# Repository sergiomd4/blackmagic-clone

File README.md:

Black Magic Clone
========================================

Black Magic is an easy-to-use board used for debugging embedded microcontrollers. It supports several targets from manufacturers such as STMicroelectronics, Atmel, Nordic Semiconductor, NXP, Texas Instruments, Freescale, Silicon Labs, Xilinx or Raspberry Pi.

GNU debugger
-------------------
The Black Magic GNU DeBugger (GDB) server features:
* Automatic target detection
* No need for target specific configuration scripts
* Easily scriptable
* Interface to the host computer does not require special drivers
* Full debugging functionality
* Works with Windows, Linux and Mac environments

Repository Contents
-------------------

* **/Production** - Gerber files, drill files, BOM, CPL file
* **/Hardware** - KiCad PCB files, footprints library
* **/Documents** - Schematics pdf

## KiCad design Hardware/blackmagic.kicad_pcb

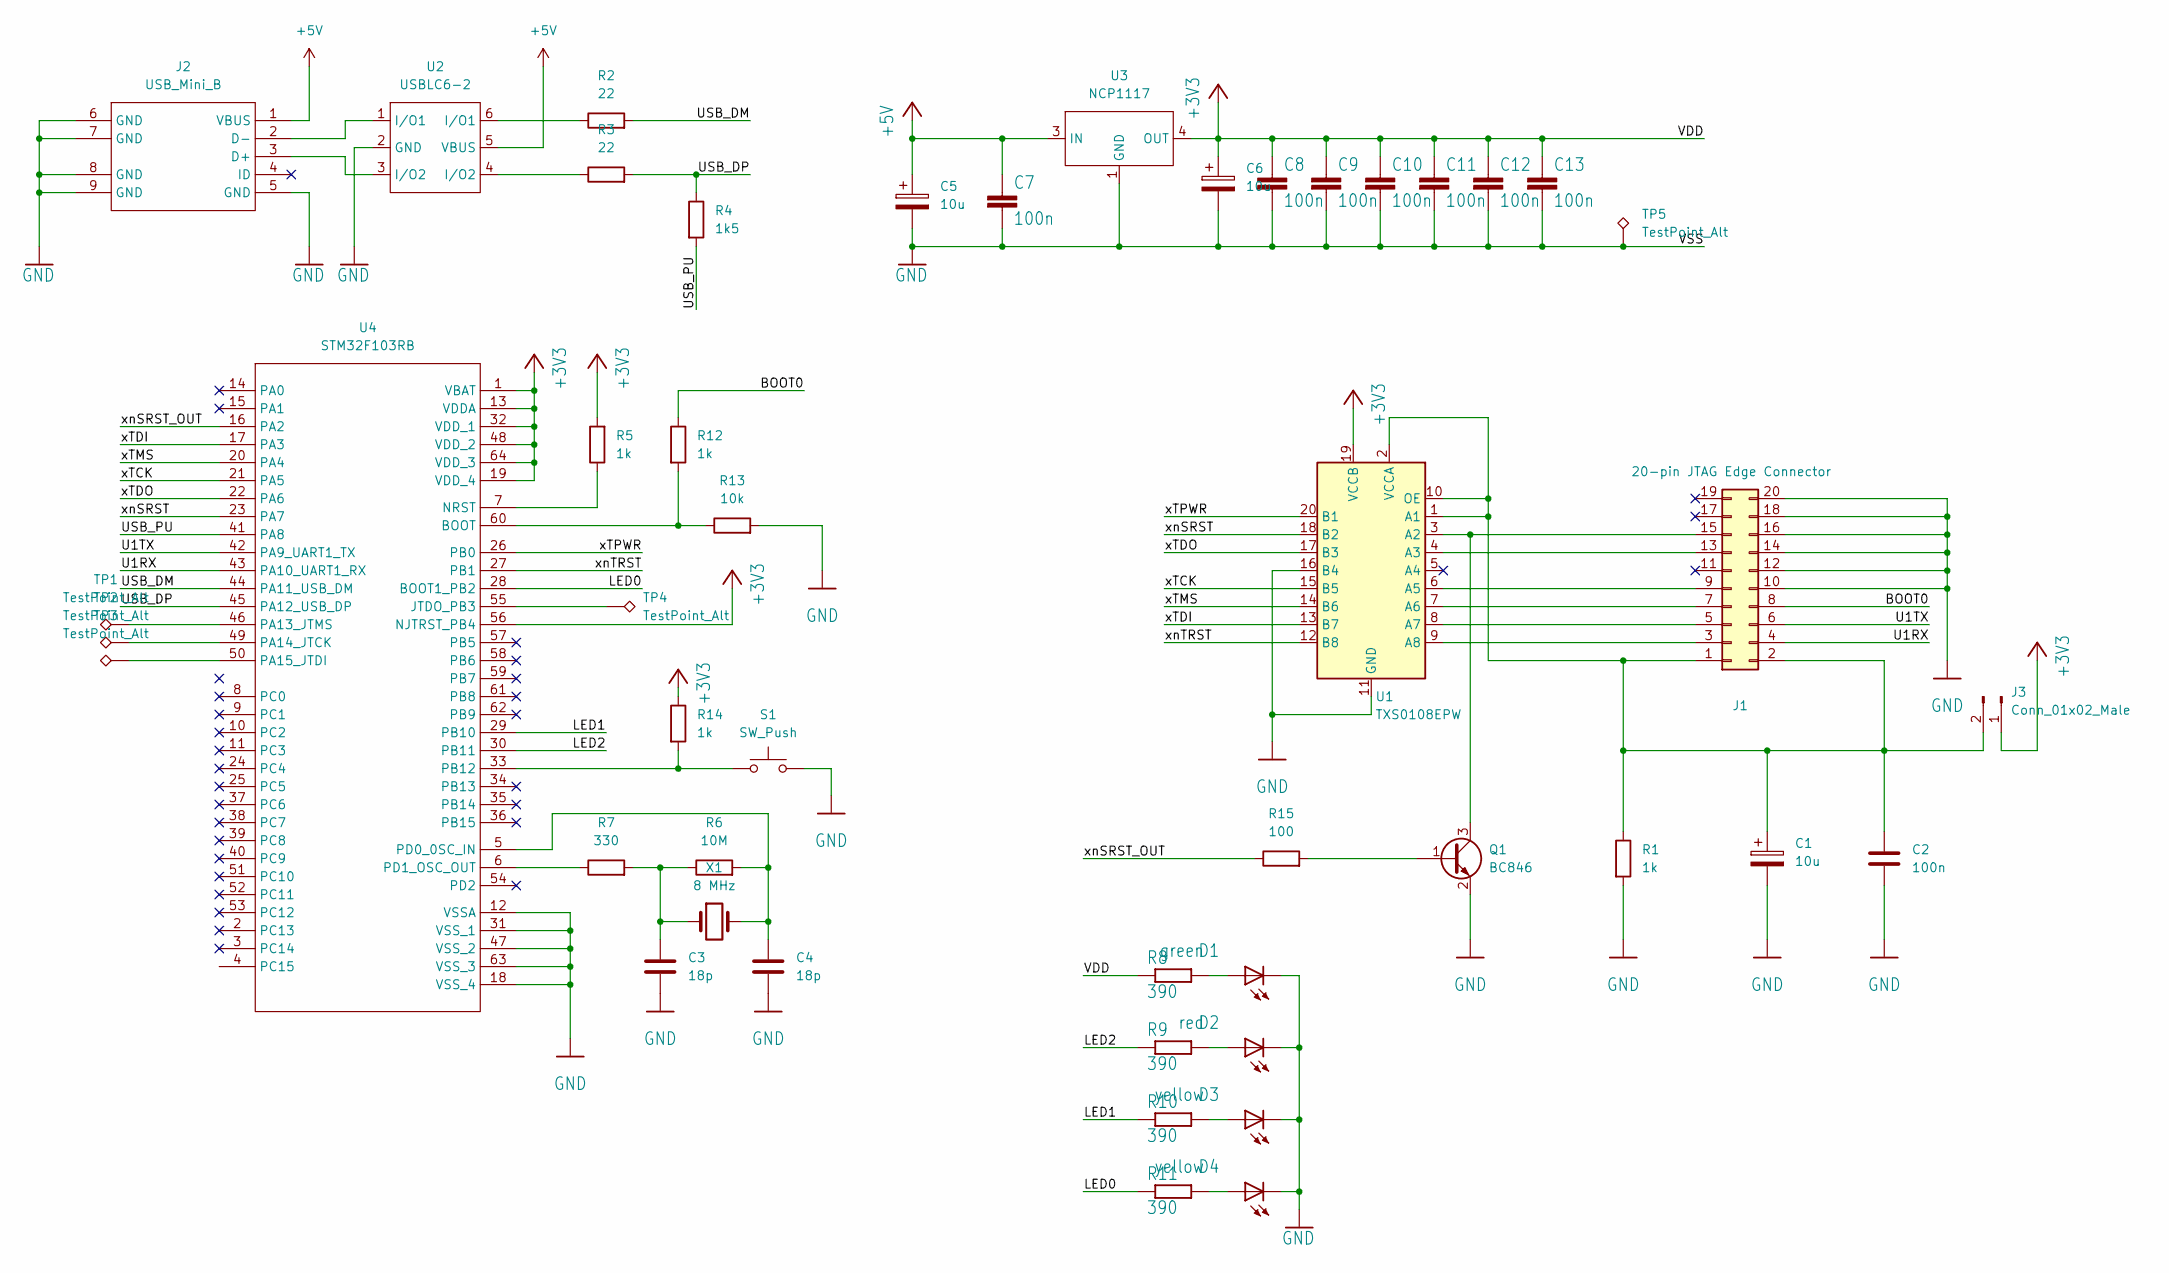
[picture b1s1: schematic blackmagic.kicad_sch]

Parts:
C1, C5, C6: 10u; CASE-A_3216; LCSC Number Part C7171
C2, C7, C8, C9, C10, C11, C12, C13: 100n; C_0603_1608Metric; LCSC Number Part C1591
C3, C4: 18p; C_0603_1608Metric; LCSC Number Part C1647
D1: green; LED_0805_2012Metric; LCSC Number Part C434432
D2: red; LED_0805_2012Metric; LCSC Number Part C434431
D3, D4: yellow; LED_0805_2012Metric; LCSC Number Part C434436
J1: 20-pin JTAG Edge Connector; PinHeader_2x10_P2.54mm_Vertical
J2: USB_Mini_B; U-M-M5SS-W-2; LCSC Number Part C91144
J3: Conn_01x02_Male; PinHeader_1x02_P2.54mm_Vertical
Q1: BC846; SOT-23; LCSC Number Part C2926206
R1, R5, R12, R14: 1k; R_0603_1608Metric; LCSC Number Part C21190
R2, R3: 22; R_0603_1608Metric; LCSC Number Part C23345
R4: 1k5; R_0603_1608Metric; LCSC Number Part C22843
R6: 10M; R_0603_1608Metric; LCSC Number Part C26097
R7: 330; R_0603_1608Metric; LCSC Number Part C23138
R8, R9, R10, R11: 390; R_0603_1608Metric; LCSC Number Part C23151
R13: 10k; R_0603_1608Metric; LCSC Number Part C25804
R15: 100; R_0603_1608Metric; LCSC Number Part C22775
S1: SW_Push; JPM1040-2013FC; LCSC Number Part C516061
TP1, TP2, TP3, TP4, TP5: TestPoint_Alt; TestPoint_Pad_1.0x1.0mm
U1: TXS0108EPW; TSSOP-20_4.4x6.5mm_P0.65mm; LCSC Number Part C17206
U2: USBLC6-2; USBLC6-2P6; LCSC Number Part C2827693
U3: NCP1117; NCP1117DT12G; LCSC Number Part C897495
U4: STM32F103RB; LQFP-64_10x10mm_P0.5mm; LCSC Number Part C8735
X1: 8 MHz; C08000J060; LCSC Number Part C259040

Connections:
+3V3: C6.1, C8.1, C9.1, C10.1, C11.1, C12.1, C13.1, J3.1, R5.2, R8.1, R14.1, U1.19 (VCCB), U3.4 (OUT), U4.1 (VBAT), U4.13 (VDDA), U4.19 (VDD_4), U4.32 (VDD_1), U4.48 (VDD_2), U4.56 (NJTRST_PB4), U4.64 (VDD_3)
+5V: C5.1, C7.1, J2.1 (VBUS), U2.5 (VBUS), U3.3 (IN)
/BOOT0: J1.8, R12.1
/LED0: R11.1, U4.28 (BOOT1_PB2)
/LED1: R10.1, U4.29 (PB10)
/LED2: R9.1, U4.30 (PB11)
/U1RX: J1.4, U4.43 (PA10_UART1_RX)
/U1TX: J1.6, U4.42 (PA9_UART1_TX)
/USB_DM: R2.2, U4.44 (PA11_USB_DM)
/USB_DP: R3.2, R4.1, U4.45 (PA12_USB_DP)
/USB_PU: R4.2, U4.41 (PA8)
/xTCK: U1.15 (B5), U4.21 (PA5)
/xTDI: U1.13 (B7), U4.17 (PA3)
/xTDO: U1.17 (B3), U4.22 (PA6)
/xTMS: U1.14 (B6), U4.20 (PA4)
/xTPWR: U1.20 (B1), U4.26 (PB0)
/xnSRST: U1.18 (B2), U4.23 (PA7)
/xnSRST_OUT: R15.1, U4.16 (PA2)
/xnTRST: U1.12 (B8), U4.27 (PB1)
GND: C1.2, C2.2, C3.2, C4.2, C5.2, C6.2, C7.2, C8.2, C9.2, C10.2, C11.2, C12.2, C13.2, D1.2 (C), D2.2 (C), D3.2 (C), D4.2 (C), J1.10, J1.12, J1.14, J1.16, J1.18, J1.20, J2.5 (GND), J2.6 (GND), J2.7 (GND), J2.8 (GND), J2.9 (GND), Q1.2 (E), R1.2, R13.2, S1.2, TP5.1, U1.11 (GND), U1.16 (B4), U2.2 (GND), U3.1 (GND), U4.12 (VSSA), U4.18 (VSS_4), U4.31 (VSS_1), U4.47 (VSS_2), U4.63 (VSS_3)
unnamed: C1.1, C2.1, J1.1, J1.2, J3.2, R1.1, U1.1 (A1), U1.2 (VCCA), U1.10 (OE)
unnamed: C3.1, R6.1, R7.2, X1.1
unnamed: C4.1, R6.2, U4.5 (PD0_0SC_IN), X1.2
unnamed: D1.1 (A), R8.2
unnamed: D2.1 (A), R9.2
unnamed: D3.1 (A), R10.2
unnamed: D4.1 (A), R11.2
unnamed: J1.3, U1.9 (A8)
unnamed: J1.5, U1.8 (A7)
unnamed: J1.7, U1.7 (A6)
unnamed: J1.9, U1.6 (A5)
unnamed: J1.13, U1.4 (A3)
unnamed: J1.15, Q1.3 (C), U1.3 (A2)
unnamed: J2.2 (D-), U2.1 (I/O1)
unnamed: J2.3 (D+), U2.3 (I/O2)
unnamed: Q1.1 (B), R15.2
unnamed: R2.1, U2.6 (I/O1)
unnamed: R3.1, U2.4 (I/O2)
unnamed: R5.1, U4.7 (NRST)
unnamed: R7.1, U4.6 (PD1_OSC_OUT)
unnamed: R12.2, R13.1, U4.60 (BOOT)
unnamed: R14.2, S1.1, U4.33 (PB12)
unnamed: TP3.1, U4.50 (PA15_JTDI)
unnamed: TP4.1, U4.55 (JTDO_PB3)
unnamed: TP1.1, U4.46 (PA13_JTMS)
unnamed: TP2.1, U4.49 (PA14_JTCK)

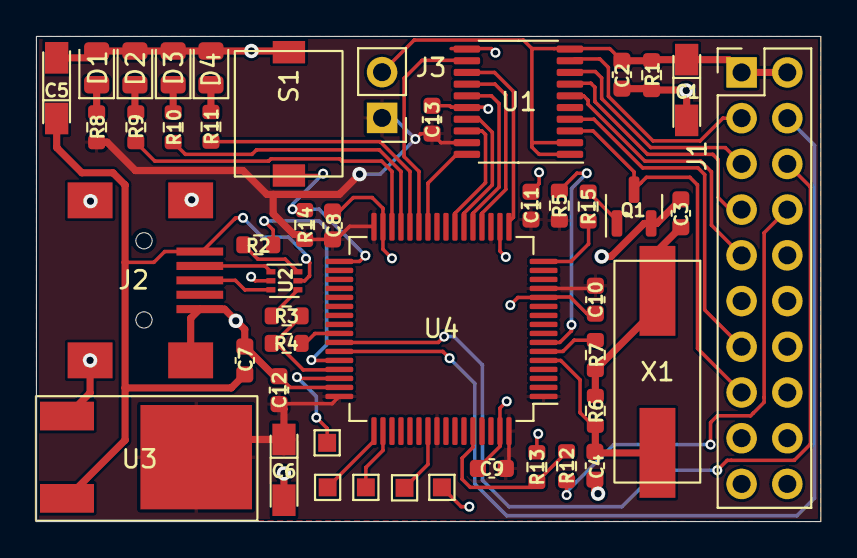
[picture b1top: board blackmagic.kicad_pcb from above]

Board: 2 copper layers, 43.6 x 27.0 mm, 47 parts (0 on the bottom side), 46 nets.

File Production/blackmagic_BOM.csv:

"Source:","C:\Users\Sergio\Documents\EOS\blackmagic-hardware-master\blackmagic_KiCAD\blackmagic.kicad_sch"
"Date:","02/09/2022 14:07:15"
"Tool:","Eeschema (6.0.7)"
"Generator:","C:\Program Files\KiCad\6.0\bin\scripting\plugins/bom_csv_grouped_by_value.py"
"Component Count:","40"

"Individual Components:"

"Item","Qty","Reference(s)","Value","LibPart","Footprint","Datasheet","LCSC Number Part"
"","","C1","10u","Device:C_Polarized","EOS:CASE-A_3216","~","C7171"
"","","C2","100n","Device:C","Capacitor_SMD:C_0603_1608Metric","~","C1591"
"","","C3","18p","Device:C","Capacitor_SMD:C_0603_1608Metric","~","C1647"
"","","C4","18p","Device:C","Capacitor_SMD:C_0603_1608Metric","~","C1647"
"","","C5","10u","Device:C_Polarized","EOS:CASE-A_3216","~","C7171"
"","","C6","10u","Device:C_Polarized","EOS:CASE-A_3216","~","C7171"
"","","C7","100n","bmp_entropia-eagle-import:C-EUC0603","Capacitor_SMD:C_0603_1608Metric","","C1591"
"","","C8","100n","bmp_entropia-eagle-import:C-EUC0603","Capacitor_SMD:C_0603_1608Metric","","C1591"
"","","C9","100n","bmp_entropia-eagle-import:C-EUC0603","Capacitor_SMD:C_0603_1608Metric","","C1591"
"","","C10","100n","bmp_entropia-eagle-import:C-EUC0603","Capacitor_SMD:C_0603_1608Metric","","C1591"
"","","C11","100n","bmp_entropia-eagle-import:C-EUC0603","Capacitor_SMD:C_0603_1608Metric","","C1591"
"","","C12","100n","bmp_entropia-eagle-import:C-EUC0603","Capacitor_SMD:C_0603_1608Metric","","C1591"
"","","C13","100n","bmp_entropia-eagle-import:C-EUC0603","Capacitor_SMD:C_0603_1608Metric","","C1591"
"","","D1","green",":LEDCHIPLED_0603_1","LED_SMD:LED_0805_2012Metric","","C434432"
"","","D2","red",":LEDCHIPLED_0603_2","LED_SMD:LED_0805_2012Metric","","C434431"
"","","D3","yellow",":LEDCHIPLED_0603_3","LED_SMD:LED_0805_2012Metric","","C434436"
"","","D4","yellow","bmp_entropia-eagle-import:LEDCHIPLED_0603","LED_SMD:LED_0805_2012Metric","","C434436"
"","","J2","USB_Mini_B",":USB_Mini_B_1","EOS:U-M-M5SS-W-2","","C91144"
"","","Q1","BC846","Transistor_BJT:BC846","Package_TO_SOT_SMD:SOT-23","https://assets.nexperia.com/documents/data-sheet/BC846_SER.pdf","C2926206"
"","","R1","1k","Device:R","Resistor_SMD:R_0603_1608Metric","~","C21190"
"","","R2","22","Device:R","Resistor_SMD:R_0603_1608Metric","~","C23345"
"","","R3","22","Device:R","Resistor_SMD:R_0603_1608Metric","~","C23345"
"","","R4","1k5","Device:R","Resistor_SMD:R_0603_1608Metric","~","C22843"
"","","R5","1k","Device:R","Resistor_SMD:R_0603_1608Metric","~","C21190"
"","","R6","10M","Device:R","Resistor_SMD:R_0603_1608Metric","~","C26097"
"","","R7","330","Device:R","Resistor_SMD:R_0603_1608Metric","~","C23138"
"","","R8","390","bmp_entropia-eagle-import:R-EU_R0603","Resistor_SMD:R_0603_1608Metric","","C23151"
"","","R9","390","bmp_entropia-eagle-import:R-EU_R0603","Resistor_SMD:R_0603_1608Metric","","C23151"
"","","R10","390","bmp_entropia-eagle-import:R-EU_R0603","Resistor_SMD:R_0603_1608Metric","","C23151"
"","","R11","390","bmp_entropia-eagle-import:R-EU_R0603","Resistor_SMD:R_0603_1608Metric","","C23151"
"","","R12","1k","Device:R","Resistor_SMD:R_0603_1608Metric","~","C21190"
"","","R13","10k","Device:R","Resistor_SMD:R_0603_1608Metric","~","C25804"
"","","R14","1k","Device:R","Resistor_SMD:R_0603_1608Metric","~","C21190"
"","","R15","100","Device:R","Resistor_SMD:R_0603_1608Metric","~","C22775"
"","","S1","SW_Push","Switch:SW_Push","EOS:JPM1040-2013FC","~","C516061"
"","","U1","TXS0108EPW","Logic_LevelTranslator:TXS0108EPW","Package_SO:TSSOP-20_4.4x6.5mm_P0.65mm","www.ti.com/lit/ds/symlink/txs0108e.pdf","C17206"
"","","U2","USBLC6-2","UNIclicker:USBLC6-2P6","EOS:USBLC6-2P6","","C2827693"
"","","U3","NCP1117","blackmagic:NCP1117","EOS:NCP1117DT12G","","C897495"
"","","U4","STM32F103RB","blackmagic:STM32F103RB","Package_QFP:LQFP-64_10x10mm_P0.5mm","","C8735"
"","","X1","8 MHz","Device:Crystal","EOS:C08000J060","~","C259040"

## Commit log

2022-09-13 Add schematic
2022-09-13 Add images
2022-09-13 Move files into folders
2022-09-13 Add KiCad files
2022-09-13 Update gitignore
2022-09-13 Add BOM
2022-09-13 Add CPL
2022-09-13 Add Drill Files
2022-09-13 Add Gerber Files
2022-09-13 Add footprints library
